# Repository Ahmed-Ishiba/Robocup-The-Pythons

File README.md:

# The pythons robocup
documentation of out project in robocup junior of me and my team the pythons that consists of me , eyad ahmed nazary and zeyad wahid each are responsible for programming electrical and mechanical respectivly we started working on this project on 28/10 and ended on 20/3 we then divided our time according to this time plan

## Time plan:

------------------------------------------------------------------------------------------------------------------------------
 
 ## design of used PCBs:
 
 ### Arduino shield:

---------------------------------------------------------------------------------------------------------------------------
 ### power distribution PCB:

### servo PCB:

-------------------------------------------------------------------------------------------------------------------

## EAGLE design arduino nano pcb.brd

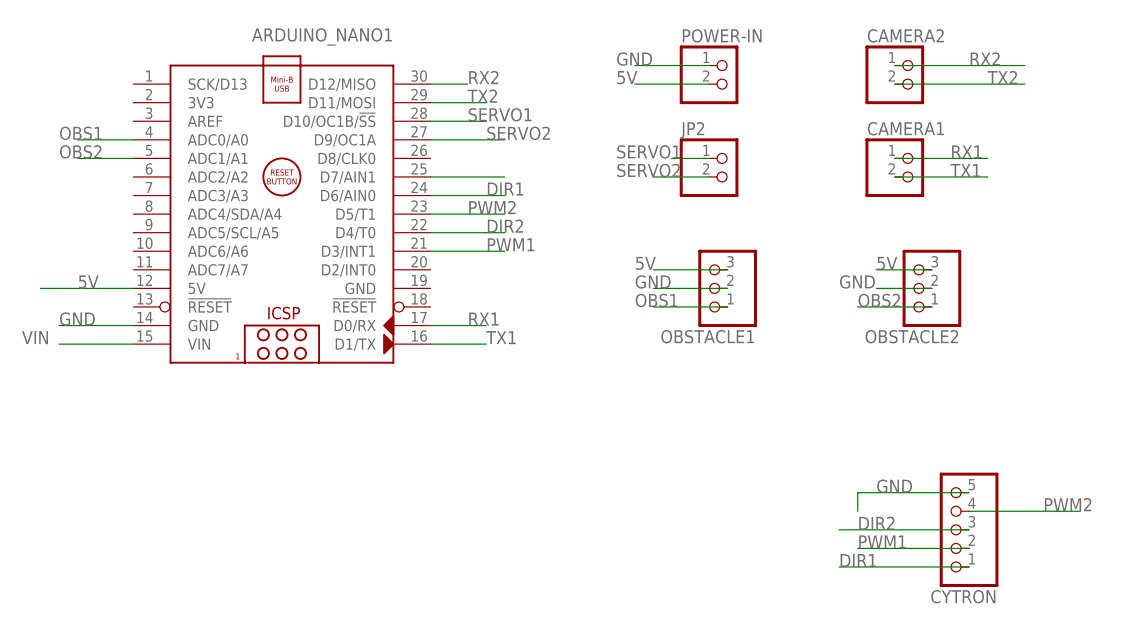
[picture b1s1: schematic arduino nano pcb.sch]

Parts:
ARDUINO_NANO1: ARDUINO_NANO
CAMERA1, CAMERA2: PINHD-1X2; 1X02
CYTRON: PINHD-1X5; 1X05
JP2: PINHD-1X2; 1X02
OBSTACLE1, OBSTACLE2: PINHD-1X3; 1X03
POWER-IN: PINHD-1X2; 1X02

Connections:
5V: ARDUINO_NANO1.12 (5V), OBSTACLE1.3, OBSTACLE2.3, POWER-IN.2
DIR1: ARDUINO_NANO1.24 (D6/AIN0), CYTRON.1
DIR2: ARDUINO_NANO1.22 (D4/T0), CYTRON.3
GND: ARDUINO_NANO1.14 (GND), ARDUINO_NANO1.19 (GND), CYTRON.5, OBSTACLE1.2, OBSTACLE2.2, POWER-IN.1
OBS1: ARDUINO_NANO1.4 (ADC0/A0), OBSTACLE1.1
OBS2: ARDUINO_NANO1.5 (ADC1/A1), OBSTACLE2.1
PWM1: ARDUINO_NANO1.21 (D3/INT1), CYTRON.2
PWM2: ARDUINO_NANO1.23 (D5/T1), CYTRON.4
RX1: ARDUINO_NANO1.17 (D0/RX), CAMERA1.1
RX2: ARDUINO_NANO1.30 (D12/MISO), CAMERA2.1
SERVO1: ARDUINO_NANO1.28 (D10/OC1B/!SS), JP2.1
SERVO2: ARDUINO_NANO1.27 (D9/OC1A), JP2.2
TX1: ARDUINO_NANO1.16 (D1/TX), CAMERA1.2
TX2: ARDUINO_NANO1.29 (D11/MOSI), CAMERA2.2
VIN: ARDUINO_NANO1.15 (VIN)

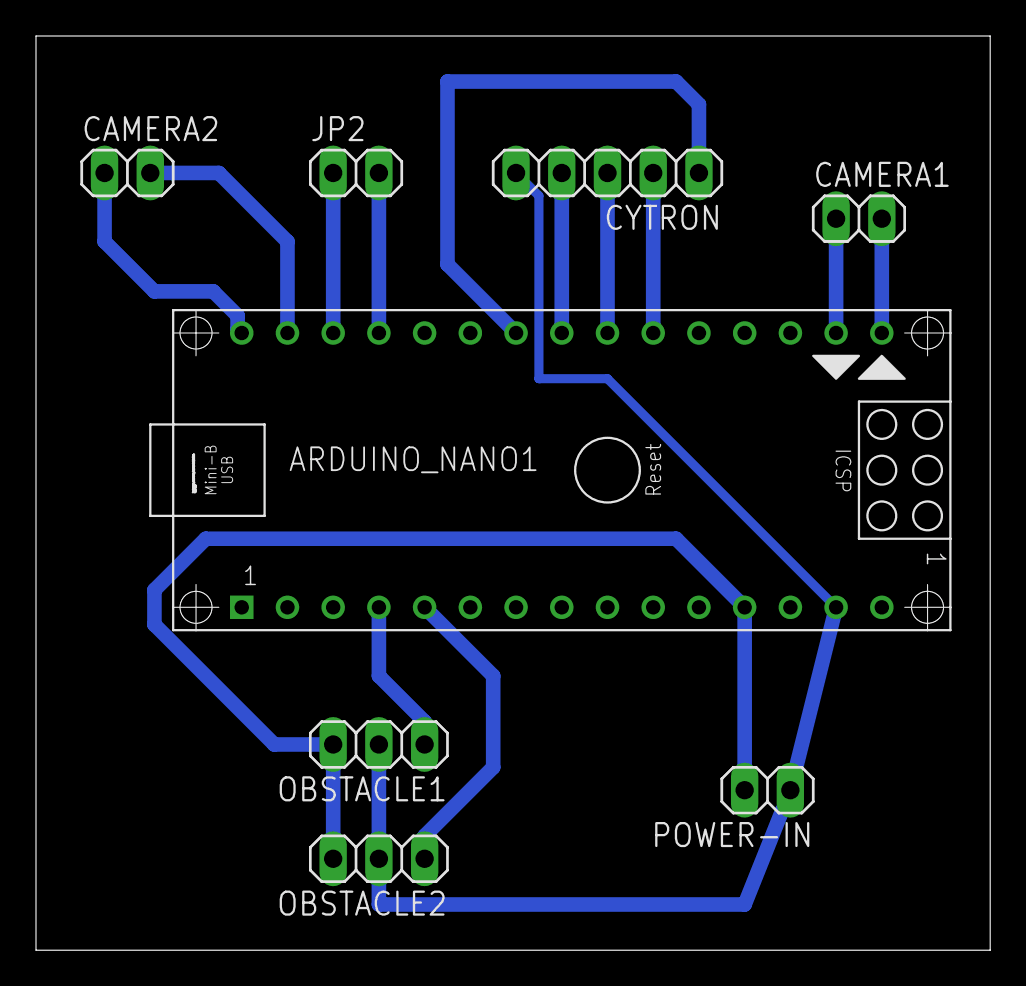
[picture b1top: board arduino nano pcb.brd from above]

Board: 2 copper layers, 53.0 x 50.8 mm, 8 parts (0 on the bottom side), 14 nets.
